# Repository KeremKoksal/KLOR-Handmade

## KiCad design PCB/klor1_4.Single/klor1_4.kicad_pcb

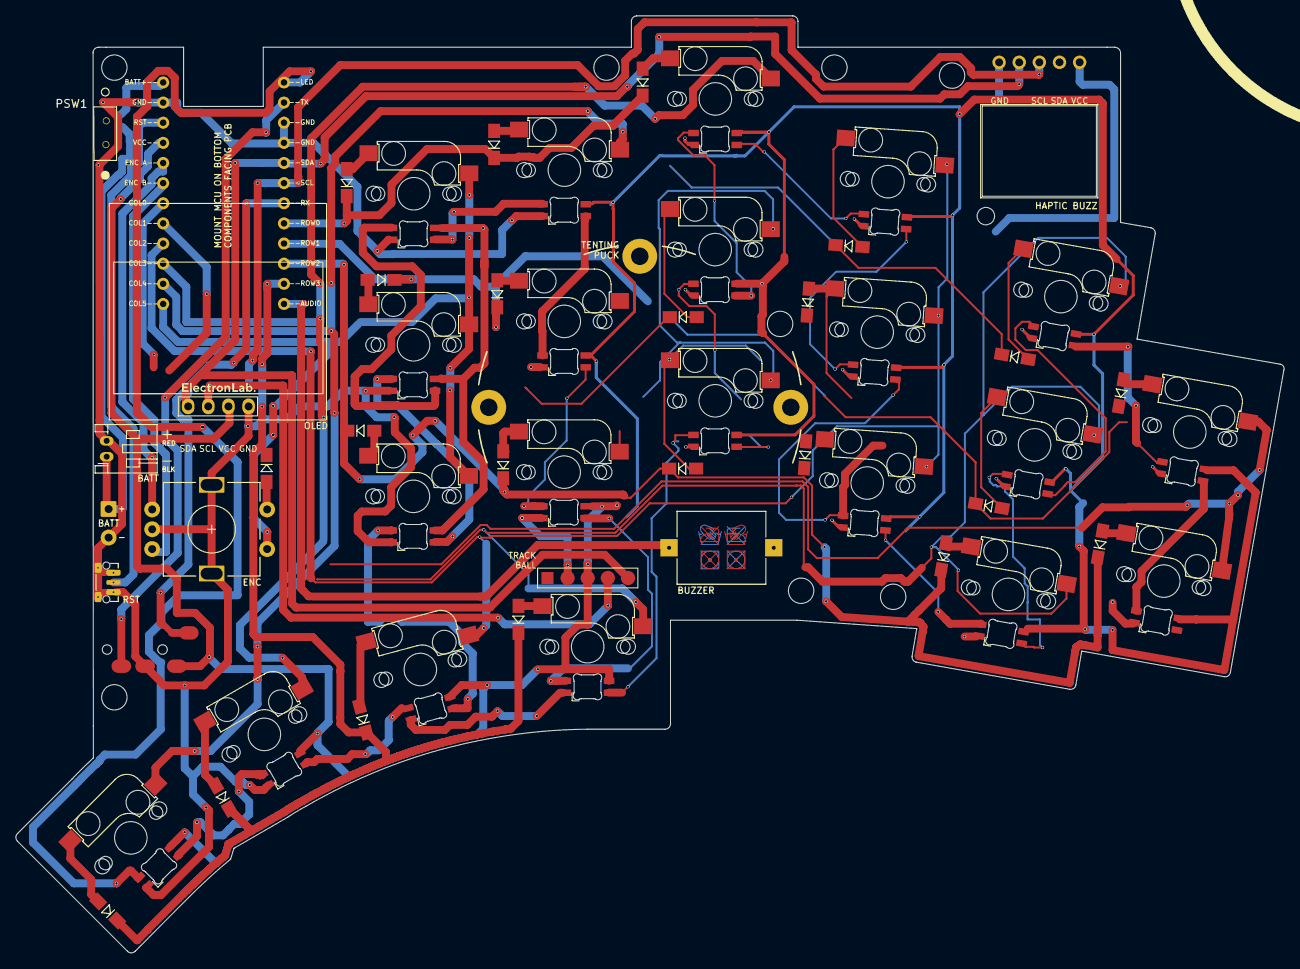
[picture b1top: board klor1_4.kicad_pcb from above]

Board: 2 copper layers, 160.0 x 118.2 mm, 63 parts (1 on the bottom side), 65 nets.

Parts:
BT1: JST Connector; JST_PH_reversible
BT2: Battery_Cell; custombatteryconnector_small
BZ1: Buzzer; Buzzer_Mallory_AST1109MLTRQ_reversible
D1, D2, D3, D4, D5, D6, D7, D8, D9, D10, D11, D12, D13, D14, D15, D16, D17, D18, D19, D20, D21, D22: D_Small; Diode_SOD123
J1: MJ-4PP-9
J2: Haptic Buzz; Pimoroni Haptic Buzz DRV2605L Driver
J3: lv27; lvc27_onlyInput
MH1, MH2, MH3, MH4, MH5, MH6, MH7, MH8: MountingHole_3.2mm_M3
MH9: MountingHole_2.2mm_M2
OLED1: SSD1306; SSD1306_128x64OLED
PSW1: SW_DPDT_x2; MSK12C02_reversible
RSW1: SW_Push; SW_Push_1P1T-MP_NO_Horizontal_Alps_SKRTLAE010_both_sides
SW1, SW2, SW3, SW4, SW5, SW6, SW7, SW8, SW9, SW10, SW11, SW12, SW13, SW14, SW15, SW16, SW17, SW19, SW20, SW21, SW22: SW_PUSH-MX_W_LED; SK6812MINI_and_cherry_1
SW18: RotaryEncoder_Switch; RotaryEncoder_Alps_EC11E-Switch_Vertical_H20mm-keebio_modif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
U1: ProMicro_Single

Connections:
+BATT: PSW1.3 (C), U1.1
/PSW: BT1.1 (+), BT2.1 (+), PSW1.2 (B)
AUDIO: BZ1.1 (-), U1.13
ENCA: SW18.A, U1.5
ENCB: SW18.B, U1.6
GND: BT1.2 (-), BT2.2 (-), BZ1.2 (+), J1.2, J2.5, J3.2, OLED1.1 (GND), PSW1.NC, RSW1.1, RSW1.MP, SW1.2 (VSS), SW2.2 (VSS), SW3.2 (VSS), SW4.2 (VSS), SW5.2 (VSS), SW6.2 (VSS), SW7.2 (VSS), SW8.2 (VSS), SW9.2 (VSS), SW10.2 (VSS), SW11.2 (VSS), SW12.2 (VSS), SW13.2 (VSS), SW14.2 (VSS), SW15.2 (VSS), SW16.2 (VSS), SW17.2 (VSS), SW18.C, SW18.MP, SW19.2 (VSS), SW20.2 (VSS), SW21.2 (VSS), SW22.2 (VSS), U1.2, U1.21, U1.22
LED: SW19.3 (DIN), U1.24
unnamed: D1.2 (A), SW1.6
unnamed: D2.2 (A), SW2.6
unnamed: D3.2 (A), SW3.6
unnamed: D4.2 (A), SW4.6
unnamed: D5.2 (A), SW5.6
unnamed: D6.2 (A), SW6.6
unnamed: D7.2 (A), SW7.6
unnamed: D8.2 (A), SW8.6
unnamed: D9.2 (A), SW9.6
unnamed: D10.2 (A), SW10.6
unnamed: D11.2 (A), SW11.6
unnamed: D12.2 (A), SW12.6
unnamed: D13.2 (A), SW13.6
unnamed: D14.2 (A), SW14.6
unnamed: D15.2 (A), SW15.6
unnamed: D16.2 (A), SW16.6
unnamed: D17.2 (A), SW17.6
unnamed: D19.2 (A), SW19.6
unnamed: D20.2 (A), SW20.6
unnamed: D21.2 (A), SW21.6
unnamed: D22.2 (A), SW22.6
unnamed: SW1.3 (DIN), SW6.1 (DOUT)
unnamed: SW1.1 (DOUT), SW2.3 (DIN)
unnamed: SW2.1 (DOUT), SW7.3 (DIN)
unnamed: SW3.3 (DIN), SW8.1 (DOUT)
unnamed: SW3.1 (DOUT), SW4.3 (DIN)
unnamed: SW4.1 (DOUT), SW9.3 (DIN)
unnamed: SW10.3 (DIN), SW16.1 (DOUT)
unnamed: SW5.3 (DIN), SW10.1 (DOUT)
unnamed: SW5.1 (DOUT), SW11.3 (DIN)
unnamed: SW11.1 (DOUT), SW17.3 (DIN)
unnamed: SW12.3 (DIN), SW21.1 (DOUT)
unnamed: SW6.3 (DIN), SW12.1 (DOUT)
unnamed: SW7.1 (DOUT), SW13.3 (DIN)
unnamed: SW13.1 (DOUT), SW22.3 (DIN)
unnamed: SW14.3 (DIN), SW22.1 (DOUT)
unnamed: SW8.3 (DIN), SW14.1 (DOUT)
unnamed: SW9.1 (DOUT), SW15.3 (DIN)
unnamed: SW15.1 (DOUT), SW16.3 (DIN)
unnamed: SW19.1 (DOUT), SW20.3 (DIN)
unnamed: SW20.1 (DOUT), SW21.3 (DIN)
RESET: RSW1.2, U1.3
RX: J1.3, U1.18
SCL: J2.3, J3.4, OLED1.3 (SCL), U1.19
SDA: J2.2, J3.5, OLED1.4 (SDA), U1.20
SW18B: D18.2 (A), SW18.S2
TX: J1.4, U1.23
VCC: J1.1, J2.1, J3.3, OLED1.2 (VCC), SW1.4 (VDD), SW2.4 (VDD), SW3.4 (VDD), SW4.4 (VDD), SW5.4 (VDD), SW6.4 (VDD), SW7.4 (VDD), SW8.4 (VDD), SW9.4 (VDD), SW10.4 (VDD), SW11.4 (VDD), SW12.4 (VDD), SW13.4 (VDD), SW14.4 (VDD), SW15.4 (VDD), SW16.4 (VDD), SW17.4 (VDD), SW19.4 (VDD), SW20.4 (VDD), SW21.4 (VDD), SW22.4 (VDD), U1.4
col0: SW11.5, SW17.5, U1.7
col1: SW5.5, SW10.5, SW16.5, SW22.5, U1.8
col2: SW4.5, SW9.5, SW15.5, SW21.5, U1.9
col3: SW3.5, SW8.5, SW14.5, SW20.5, U1.10
col4: SW2.5, SW7.5, SW13.5, SW19.5, U1.11
col5: SW1.5, SW6.5, SW12.5, SW18.S1, U1.12
row0: D1.1 (K), D2.1 (K), D3.1 (K), D4.1 (K), D5.1 (K), U1.17
row1: D6.1 (K), D7.1 (K), D8.1 (K), D9.1 (K), D10.1 (K), D11.1 (K), U1.16
row2: D12.1 (K), D13.1 (K), D14.1 (K), D15.1 (K), D16.1 (K), D17.1 (K), U1.15
row3: D18.1 (K), D19.1 (K), D20.1 (K), D21.1 (K), D22.1 (K), U1.14

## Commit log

2024-07-09 modifié : PCB/klor1_3/KLOR.pretty/MJ-4PP-9.kicad_mod modifié : PCB/klor1_3/fp-info-cache modifié : PCB/klor1_3/gerbers/klor1_3-B_Cu.gbl modifié : PCB/klor1_3/gerbers/klor1_3-B_Mask.gbs modifié : PCB/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
2024-07-09 nouveau fichier : gerbers.zip nouveau fichier : ../klor1_3.kicad_dru
2024-07-25 modifié : PCB/klor1_3/KLOR.pretty/SK6812MINI_and_cherry.kicad_mod nouveau fichier : PCB/klor1_3/klor1_3-backups/klor1_3-2024-07-23_162032.zip modifié : PCB/klor1_3/klor1_3.kicad_pro nouveau fichier :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
2024-07-25 nouveau fichier : PCB/klor1_4/klor1_4-backups/klor1_4-2024-07-25_133230.zip nouveau fichier : docs/images/Klor_1.4_picture1.png nouveau fichier : docs/images/Klor_1.4_picture2.png supprimé : PCB/klor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
2024-07-25 supprimé : PCB/klor1_4/_autosave-klor1_4.kicad_pcb supprimé : PCB/klor1_4/klor1_4-backups/klor1_4-2024-07-25_065953.zip supprimé : PCB/klor1_4/~_autosave-klor1_4.kicad_pcb.lck
2024-07-25 nouveau fichier : PCB/klor1_4/_autosave-klor1_4.kicad_pcb modifié : PCB/klor1_4/gerbers/gerbers.zip modifié : PCB/klor1_4/gerbers/klor1_4-B_Cu.gbl modifié : PCB/klor1_4/gerbers/klor1_4-B_Mask.gbs mod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
2024-07-25 nouveau fichier : FIRMWARE/build.yaml nouveau fichier : FIRMWARE/config/boards/shields/klor/Kconfig.defconfig nouveau fichier : FIRMWARE/config/boards/shields/klor/Kconfig.shield nouveau fichier : FI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
2024-07-25 modifié : PCB/klor1_3/klor1_3.kicad_prl modifié : PCB/klor1_4/klor1_4.kicad_pcb modifié : PCB/klor1_4/klor1_4.kicad_prl modifié : PCB/klor1_4/klor1_4.kicad_pro supprimé : PCB/klor1_4/~klor1_3.kicad_p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
2024-07-25 supprimé : PCB/klor1_4/KLOR_1-3_gerbers.zip modifié : PCB/klor1_4/klor1_4.kicad_prl
2024-07-25 supprimé : klor.keymap~
2024-07-25 supprimé : nice_nano_v2.overlay~
2024-07-26 modifié : klor.keymap
2024-07-26 modifié : gerbers.zip modifié : klor1_4-B_Cu.gbl modifié : klor1_4-B_Mask.gbs modifié : klor1_4-B_Paste.gbp modifié : klor1_4-B_Silkscreen.gbo modifié : klor1_4-Edge_Cuts.gm1 modifié : klor1_4-F_Cu.g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
2024-07-30 modifié : FIRMWARE/config/boards/shields/klor/boards/nice_nano_v2.overlay modifié : FIRMWARE/config/boards/shields/klor/klor.dtsi modifié : FIRMWARE/config/boards/shields/klor/klor_common.dtsi modifi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
2024-07-30 modifié : PCB/klor1_4/KLOR.pretty/Buzzer_Mallory_AST1109MLTRQ_reversible.kicad_mod modifié : PCB/klor1_4/KLOR.pretty/Diode_SOD123.kicad_mod modifié : PCB/klor1_4/KLOR.pretty/SK6812MINI_and_cherry_1.k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
2024-07-30 modifié : PCB/klor1_4/klor1_4.kicad_pcb modifié : docs/images/Klor_1.4_picture1.png modifié : docs/images/Klor_1.4_picture2.png
2024-07-30 modifié : PCB/klor1_4/gerbers/gerbers.zip modifié : PCB/klor1_4/gerbers/klor1_4-B_Cu.gbl modifié : PCB/klor1_4/gerbers/klor1_4-B_Mask.gbs modifié : PCB/klor1_4/gerbers/klor1_4-B_Paste.gbp modifié : P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
2024-07-30 modifié : PCB/klor1_4/klor1_4.kicad_pcb modifié : PCB/klor1_4/klor1_4.kicad_prl modifié : PCB/klor1_4/klor1_4.kicad_pro
2024-08-08 nouveau fichier : Klor_1.4_picture4.png nouveau fichier : Klor_1.4_picture5.png nouveau fichier : Klor_1.4_picture6.jpg
2024-08-09 Update README.md
    Added fabrication notes and link to FW fork
2024-08-09 nouveau fichier : PCB/Alternate DIY Haptic Module/Gerber_Haptic-Module_Haptic-Module_2024-08-09.zip nouveau fichier : case/Alternate Case Design/535004-case-designs-for-klor-polydactyl-konrad-yubitsu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
2024-08-09 Update README.md
    Inclusion of DIY haptic module. Correction of PCB for stock module
2024-08-09 supprimé : ../PCB/klor1_3/klor1_3-backups/klor1_3-2024-07-06_111804.zip supprimé : ../PCB/klor1_3/klor1_3-backups/klor1_3-2024-07-06_112832.zip supprimé : ../PCB/klor1_3/klor1_3-backups/klor1_3-2024-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
2024-08-09 supprimé : case-designs-for-klor-polydactyl-konrad-yubitsume-and-saegewerk-model_files/535004-case-designs-for-klor-polydactyl-konrad-yubitsume-and-saegewerk-2240062f-93fd-4992-ab70-c1e3f6eb6469.pdf 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
2024-08-09 modifié : ../PCB/klor1_4/fp-info-cache modifié : ../PCB/klor1_4/gerbers/gerbers.zip modifié : ../PCB/klor1_4/gerbers/klor1_4-B_Cu.gbl modifié : ../PCB/klor1_4/gerbers/klor1_4-B_Mask.gbs modifié : ../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
2024-08-09 modifié : ../PCB/Alternate DIY Haptic Module/Gerber_Haptic-Module_Haptic-Module_2024-08-09.zip
2024-08-09 supprimé : ../PCB/klor1_4/klor1_4-backups/klor1_4-2024-07-25_161157.zip supprimé : ../PCB/klor1_4/klor1_4-backups/klor1_4-2024-07-25_161736.zip supprimé : ../PCB/klor1_4/klor1_4-backups/klor1_4-2024-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
2024-08-10 modifié : PCB/klor1_4/klor1_4.kicad_prl modifié : docs/images/Klor_1.4_picture1.png modifié : docs/images/Klor_1.4_picture2.png modifié : docs/images/Klor_1.4_picture3.png
2024-08-10 modifié : FIRMWARE/config/klor.keymap modifié : PCB/klor1_4/klor1_4.kicad_prl
2024-08-23 nouveau fichier : FIRMWARE/qmk_rp2040/klor/config.h nouveau fichier : FIRMWARE/qmk_rp2040/klor/info.json nouveau fichier : FIRMWARE/qmk_rp2040/klor/keyboard.json nouveau fichier : FIRMWARE/qmk_rp2040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
2024-08-23 supprimé : FIRMWARE/build.yaml supprimé : FIRMWARE/config/boards/shields/klor/Kconfig.defconfig supprimé : FIRMWARE/config/boards/shields/klor/Kconfig.shield supprimé : FIRMWARE/config/boards/shields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
2024-08-24 modifié : FIRMWARE/qmk_rp2040/klor/info.json modifié : FIRMWARE/qmk_rp2040/klor/keyboard.json nouveau fichier : FIRMWARE/qmk_rp2040/klor/keymaps/via/keymap.c nouveau fichier : FIRMWARE/qmk_rp2040/klo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
2024-08-24 nouveau fichier : FIRMWARE/Ready-to-flash/qmk-RP2040/klor_default.uf2 nouveau fichier : FIRMWARE/Ready-to-flash/zmk-NiceNanoV2/klor_left-nice_nano_v2-zmk.uf2 nouveau fichier : FIRMWARE/Ready-to-flash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
2024-08-24 supprimé : FIRMWARE/zmk/docs/images/klor-font-logo-bright.svg supprimé : FIRMWARE/zmk/docs/images/klor-font-logo-dark.svg supprimé : FIRMWARE/zmk/docs/images/klor-layouts.svg supprimé : FIRMWARE/zmk/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
2024-08-27 nouveau fichier : PCB/klor1_4_LP_KS33/KLOR.pretty/Buzzer_Mallory_AST1109MLTRQ_reversible.kicad_mod nouveau fichier : PCB/klor1_4_LP_KS33/KLOR.pretty/Diode_SOD123.kicad_mod nouveau fichier : PCB/klor1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
2024-08-27 modifié : PCB/klor1_3/gerbers/gerbers.zip modifié : PCB/klor1_3/gerbers/klor1_3-B_Cu.gbl modifié : PCB/klor1_3/gerbers/klor1_3-B_Mask.gbs modifié : PCB/klor1_3/gerbers/klor1_3-B_Paste.gbp modifié : P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
2024-08-27 supprimé : PCB/klor1_3/KLOR_1-3_gerbers.zip
2024-08-27 nouveau fichier : docs/images/Klor_1.4_picture7.png nouveau fichier : docs/images/Klor_1.4_picture8.png nouveau fichier : docs/images/Klor_1.4_picture9.png
2024-08-27 nouveau fichier : docs/images/Klor_1.4_picture10.png nouveau fichier : docs/images/Klor_1.4_picture11.png nouveau fichier : docs/images/Klor_1.4_picture12.png
2024-08-28 supprimé : FIRMWARE/Ready-to-flash/qmk-RP2040/klor_default.uf2 modifié : FIRMWARE/qmk_rp2040/klor/config.h modifié : FIRMWARE/qmk_rp2040/klor/keyboard.json modifié : FIRMWARE/qmk_rp2040/klor/keymaps/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
2024-08-28 nouveau fichier : FIRMWARE/Ready-to-flash/qmk-RP2040/klor_default_crossed_serial.uf2 nouveau fichier : FIRMWARE/Ready-to-flash/qmk-RP2040/klor_default_mirror_serial.uf2
2024-08-28 Update CHANGELOG.md
    Correction of the wiring error of the 1.3 original design for serial communication. Correction was made to both 1.4 versions but NOT on the 1.3 version provided on this fork.
2024-08-28 modifié : FIRMWARE/qmk_rp2040/klor/config.h supprimé : FIRMWARE/qmk_rp2040/klor/info.json modifié : FIRMWARE/qmk_rp2040/klor/keyboard.json modifié : FIRMWARE/qmk_rp2040/klor/keymaps/default/rules.mk 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
2024-08-28 modifié : FIRMWARE/Ready-to-flash/qmk-RP2040/klor_default_mirror_serial.uf2 modifié : FIRMWARE/qmk_rp2040/klor/config.h modifié : FIRMWARE/qmk_rp2040/klor/keyboard.json modifié : FIRMWARE/qmk_rp2040/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
2024-08-29 modifié : FIRMWARE/Ready-to-flash/qmk-RP2040/klor_default_mirror_serial.uf2 modifié : FIRMWARE/qmk_rp2040/klor/config.h modifié : FIRMWARE/qmk_rp2040/klor/keyboard.json modifié : FIRMWARE/qmk_rp2040/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
2024-08-29 renommé : FIRMWARE/Ready-to-flash/qmk-RP2040/klor_default_mirror_serial.uf2 -> FIRMWARE/Ready-to-flash/qmk-RP2040/klor_default.uf2 supprimé : FIRMWARE/Ready-to-flash/qmk-RP2040/klor_default_crossed_s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
2024-08-29 modifié : PCB/klor1_4_LP_KS33/KLOR.pretty/MJ-4PP-9.kicad_mod supprimé : PCB/klor1_4_LP_KS33/README.md modifié : PCB/klor1_4_LP_KS33/fp-info-cache modifié : PCB/klor1_4_LP_KS33/gerbers/gerbers.zip mod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
2024-08-31 modifié : PCB/klor1_4/klor1_4.kicad_prl
2024-08-31 modifié : FIRMWARE/qmk_rp2040/klor/config.h modifié : FIRMWARE/qmk_rp2040/klor/keymaps/default/config.h modifié : FIRMWARE/qmk_rp2040/klor/keymaps/default/keymap.c supprimé : FIRMWARE/qmk_rp2040/klor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
2024-08-31 nouveau fichier : FIRMWARE/Ready-to-flash/qmk-RP2040/QMK/klor_default_left.uf2 renommé : FIRMWARE/Ready-to-flash/qmk-RP2040/klor_default.uf2 -> FIRMWARE/Ready-to-flash/qmk-RP2040/QMK/klor_default_mas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
2024-08-31 nouveau fichier : FIRMWARE/qmk_rp2040/klor/keymaps/vial/config.h nouveau fichier : FIRMWARE/qmk_rp2040/klor/keymaps/vial/keymap.c nouveau fichier : FIRMWARE/qmk_rp2040/klor/keymaps/vial/klor.vil nouv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
2024-08-31 nouveau fichier : docs/images/Klor_1.4_picture13.png
2024-09-03 nouveau fichier : PCB/klor1_4_LP_KS33/KLOR.pretty/KS33_Symetrical.kicad_mod modifié : PCB/klor1_4_LP_KS33/fp-info-cache modifié : PCB/klor1_4_LP_KS33/gerbers/gerbers.zip renommé : PCB/klor1_4_LP_KS33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
2024-09-07 nouveau fichier : FIRMWARE/qmk_rp2040/electronlab/klor/config.h nouveau fichier : FIRMWARE/qmk_rp2040/electronlab/klor/halconf.h nouveau fichier : FIRMWARE/qmk_rp2040/electronlab/klor/keyboard.json r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
2024-09-07 supprimé : config.h~ supprimé : halconf.h~ supprimé : info.json~ supprimé : keyboard.json~ supprimé : keymaps/default/config.h~ supprimé : keymaps/default/keymap.c~ supprimé : keymaps/default/rules.m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
2024-09-07 supprimé : glcdfont.c~
2024-09-07 nouveau fichier : ../../../../../docs/images/KLOR_1.5.png
2024-09-10 nouveau fichier : docs/images/KLOR_1.5_picture1.png nouveau fichier : docs/images/KLOR_1.5_picture2.png nouveau fichier : docs/images/KLOR_1.5_picture3.png nouveau fichier : docs/images/KLOR_1.5_pict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
2024-09-10 modifié : FIRMWARE/qmk_rp2040/electronlab/klor/keymaps/vial/keymap.c modifié : FIRMWARE/qmk_rp2040/electronlab/klor/keymaps/vial/klor.vil
2025-04-15 Single for handmade pcb, start
2025-04-15 single mcu
2025-04-15 single 2504151724
2025-04-15 202504152355
2025-04-16 202504170029
2025-04-17 2504171658
2025-04-17 2504180105
2025-04-18 tümünü temizlemeden önce
2025-04-18 yolsuz
2025-04-18 Temiz başlangıç ile - 1
2025-04-18 left done
